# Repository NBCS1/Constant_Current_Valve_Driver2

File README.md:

# Constant_Current_Valve_Driver
Harware and firmware associated with controlling 4 bistable valves from TTL pulse of various duration. The Pulse is coming from a Pressure controller and its software were only the duration can be set. Different durations trigger different combinations of valves in the context of a microfluidic system.
The valves are bistable and require a pulse of constant current to turn ON/OFF. 
The code can be modified to have any pulse duration and the hardware can be modified to also obtain stable current from 0 to 1.5A.
The stable current is based on a AL8860 ic.

Disclaimer: We will not be responsible in case any implementation of the content of this repository leads to damage in instruments or components.

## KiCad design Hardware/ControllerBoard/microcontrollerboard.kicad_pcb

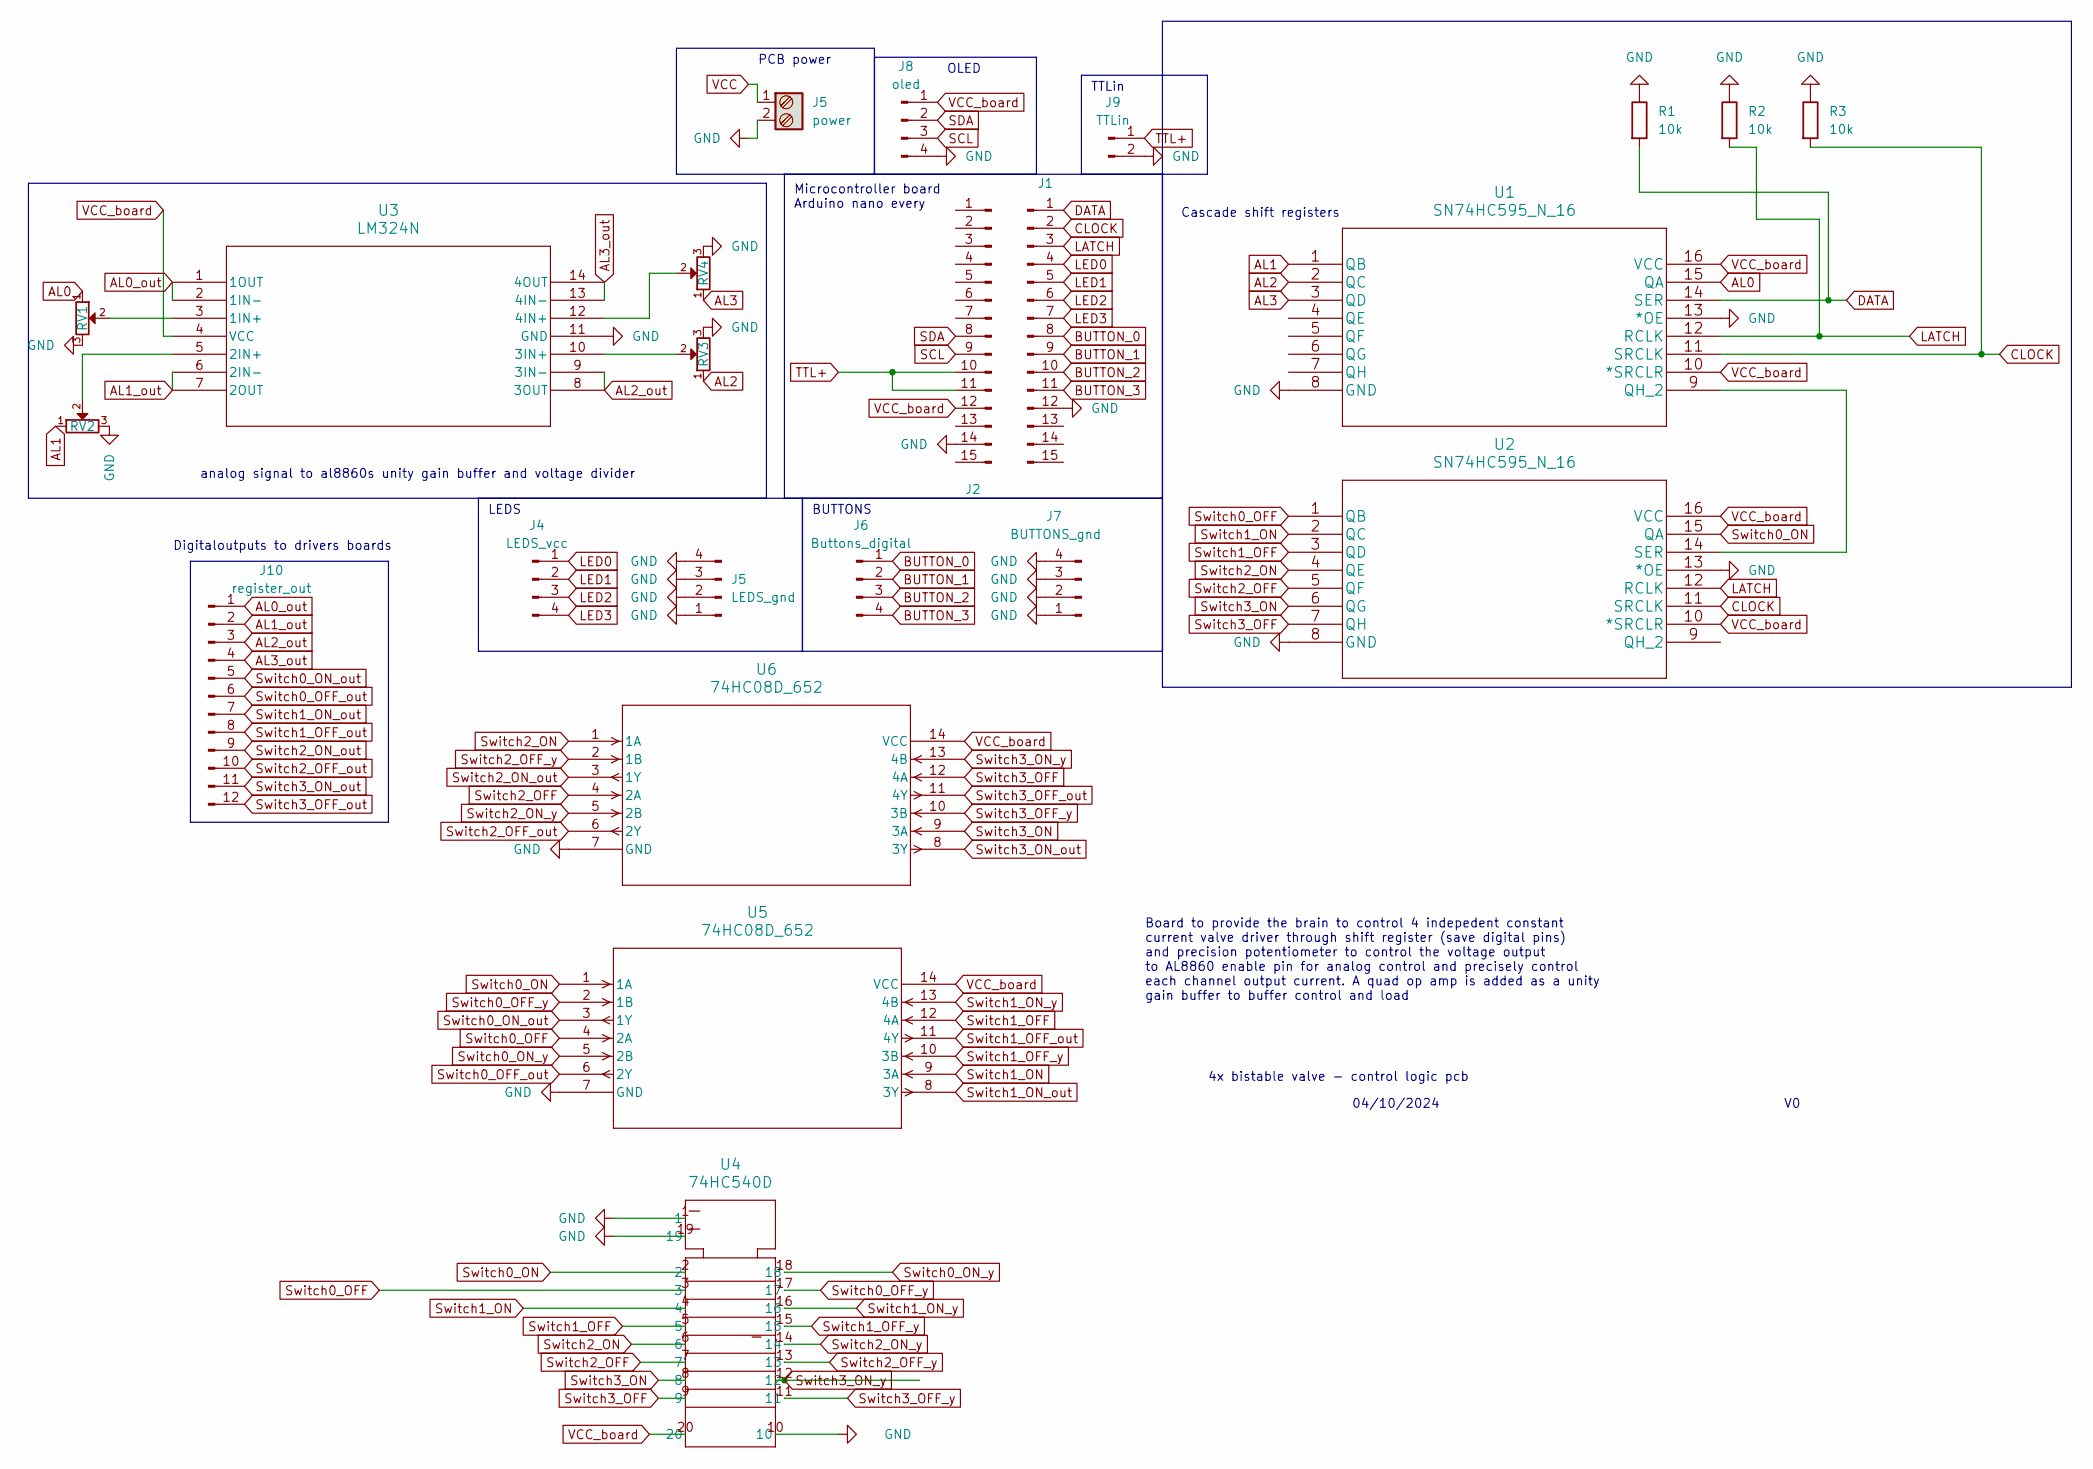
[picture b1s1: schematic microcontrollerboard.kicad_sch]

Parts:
J1, J2: Conn_01x15_Pin; PinHeader_1x15_P2.54mm_Vertical
J4: LEDS_vcc; PinSocket_1x04_P2.54mm_Vertical
J5: power; TerminalBlock_Phoenix_PT-1,5-2-5.0-H_1x02_P5.00mm_Horizontal
J6: Buttons_digital; PinSocket_1x04_P2.54mm_Vertical
J7: BUTTONS_gnd; PinSocket_1x04_P2.54mm_Vertical
J8: oled; PinSocket_1x04_P2.54mm_Vertical
J9: TTLin; PinSocket_1x02_P2.54mm_Vertical
J10: register_out; PinSocket_1x12_P2.54mm_Vertical
R1, R2, R3: 10k; R_1206_3216Metric_Pad1.30x1.75mm_HandSolder
RV1, RV2, RV3, RV4: potentiometer_3362P; Potentiometer_Vishay_T73XW_Horizontal
U1, U2: SN74HC595_N_16; D16-M
U3: LM324N; D14-M
U4: 74HC540D; SOIC20
U5, U6: 74HC08D_652; SOT108-1_NEX-M

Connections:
AL0: RV1.1, U1.15 (QA)
AL0_out: J10.1, U3.1 (1OUT), U3.2 (1IN-)
AL1: RV2.1, U1.1 (QB)
AL1_out: J10.2, U3.6 (2IN-), U3.7 (2OUT)
AL2: RV3.1, U1.2 (QC)
AL2_out: J10.3, U3.8 (3OUT), U3.9 (3IN-)
AL3: RV4.1, U1.3 (QD)
AL3_out: J10.4, U3.13 (4IN-), U3.14 (4OUT)
BUTTON_0: J1.8, J6.1
BUTTON_1: J1.9, J6.2
BUTTON_2: J1.10, J6.3
BUTTON_3: J1.11, J6.4
CLOCK: J1.2, R3.2, U1.11 (SRCLK), U2.11 (SRCLK)
DATA: J1.1, R1.2, U1.14 (SER)
LATCH: J1.3, R2.2, U1.12 (RCLK), U2.12 (RCLK)
LED0: J1.4, J4.1
LED1: J1.5, J4.2
LED2: J1.6, J4.3
LED3: J1.7, J4.4
unnamed: U1.9 (QH_2), U2.14 (SER)
unnamed: RV1.2, U3.3 (1IN+)
unnamed: RV2.2, U3.5 (2IN+)
unnamed: RV3.2, U3.10 (3IN+)
unnamed: RV4.2, U3.12 (4IN+)
SCL: J2.9, J8.3
SDA: J2.8, J8.2
Switch0_OFF: U2.1 (QB), U4.3, U5.4 (2A)
Switch0_OFF_out: J10.6, U5.6 (2Y)
Switch0_OFF_y: U4.17, U5.2 (1B)
Switch0_ON: U2.15 (QA), U4.2, U5.1 (1A)
Switch0_ON_out: J10.5, U5.3 (1Y)
Switch0_ON_y: U4.18, U5.5 (2B)
Switch1_OFF: U2.3 (QD), U4.5, U5.12 (4A)
Switch1_OFF_out: J10.8, U5.11 (4Y)
Switch1_OFF_y: U4.15, U5.10 (3B)
Switch1_ON: U2.2 (QC), U4.4, U5.9 (3A)
Switch1_ON_out: J10.7, U5.8 (3Y)
Switch1_ON_y: U4.16, U5.13 (4B)
Switch2_OFF: U2.5 (QF), U4.7, U6.4 (2A)
Switch2_OFF_out: J10.10, U6.6 (2Y)
Switch2_OFF_y: U4.13, U6.2 (1B)
Switch2_ON: U2.4 (QE), U4.6, U6.1 (1A)
Switch2_ON_out: J10.9, U6.3 (1Y)
Switch2_ON_y: U4.14, U6.5 (2B)
Switch3_OFF: U2.7 (QH), U4.9, U6.12 (4A)
Switch3_OFF_out: J10.12, U6.11 (4Y)
Switch3_OFF_y: U4.11, U6.10 (3B)
Switch3_ON: U2.6 (QG), U4.8, U6.9 (3A)
Switch3_ON_out: J10.11, U6.8 (3Y)
Switch3_ON_y: U4.12, U6.13 (4B)
TTL+: J2.10, J2.11, J9.1
VCC_board: J2.12, J8.1, U1.10 (*SRCLR), U1.16 (VCC), U2.10 (*SRCLR), U2.16 (VCC), U3.4 (VCC), U4.20, U5.14 (VCC), U6.14 (VCC)

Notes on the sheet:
Digitaloutputs to drivers boards
Cascade shift registers
04/10/2024
Board to provide the brain to control 4 indepedent constant current valve driver through shift register (save digital pins) and precision potentiometer to control the voltage output to AL8860 enable pin for analog control and precisely control each channel output current. A quad op amp is added as 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
PCB power
BUTTONS
OLED
Microcontroller board Arduino nano every
analog signal to al8860s unity gain buffer and voltage divider
LEDS
TTLin
4x bistable valve - control logic pcb

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
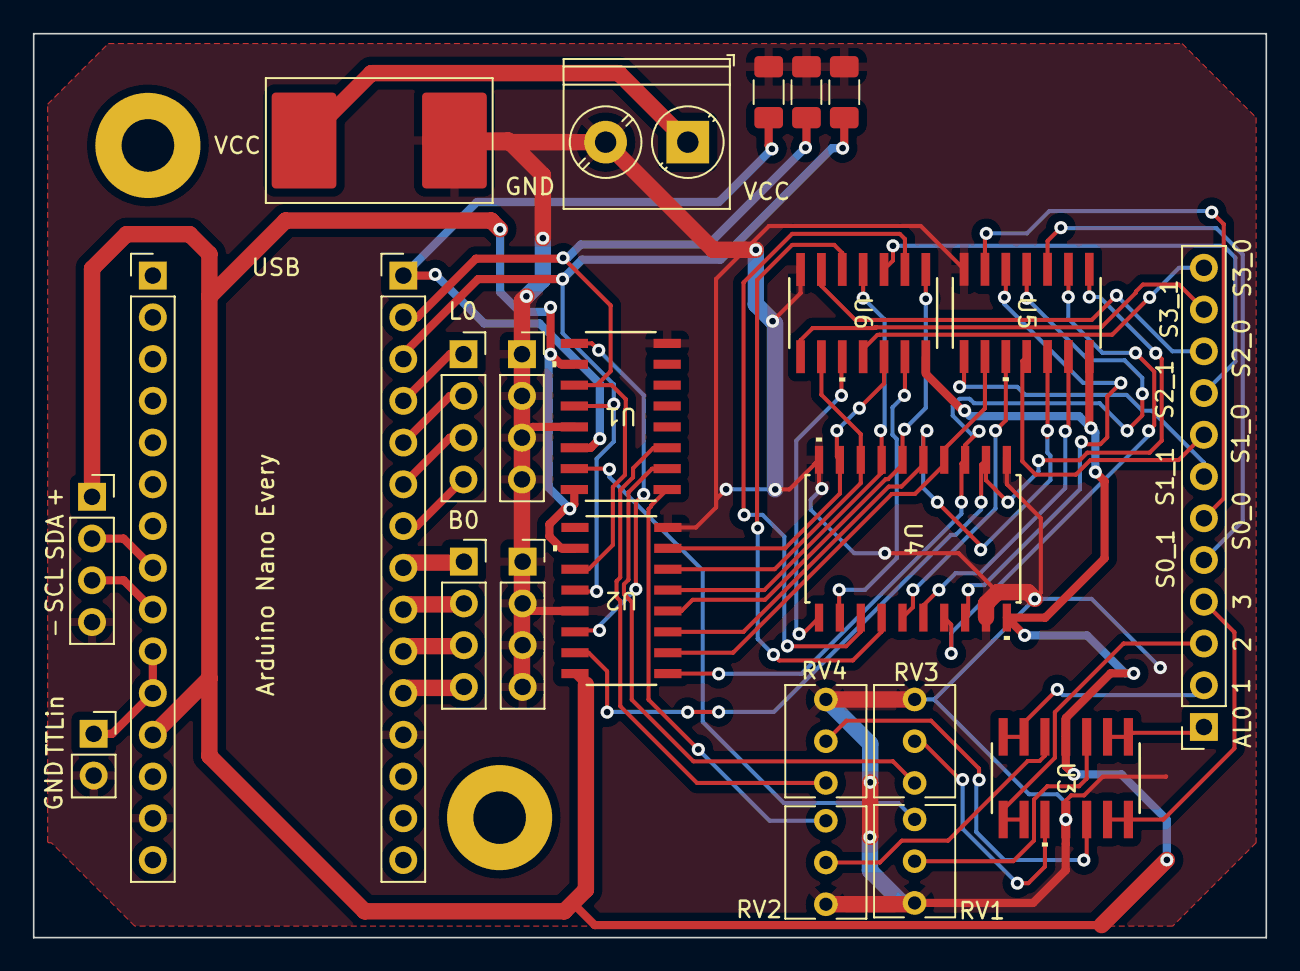
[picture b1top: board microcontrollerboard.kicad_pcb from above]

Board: 2 copper layers, 75.0 x 55.0 mm, 23 parts (0 on the bottom side), 53 nets.

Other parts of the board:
J3: power; TerminalBlock_Phoenix_PT-1,5-2-5.0-H_1x02_P5.00mm_Horizontal

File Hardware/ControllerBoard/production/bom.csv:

Designator;Footprint;Quantity;Value;LCSC Part #
J1, J2;PinHeader_1x15_P2.54mm_Vertical;2;Conn_01x15_Pin;
J10;PinSocket_1x12_P2.54mm_Vertical;1;register_out;
J3;TerminalBlock_Phoenix_PT-1,5-2-5.0-H_1x02_P5.00mm_Horizontal;1;power;
J4;PinSocket_1x04_P2.54mm_Vertical;1;LEDS_vcc;
J5;PinSocket_1x04_P2.54mm_Vertical;1;LEDS_gnd;
J6;PinSocket_1x04_P2.54mm_Vertical;1;Buttons_digital;
J7;PinSocket_1x04_P2.54mm_Vertical;1;BUTTONS_gnd;
J8;PinSocket_1x04_P2.54mm_Vertical;1;oled;
J9;PinSocket_1x02_P2.54mm_Vertical;1;TTLin;
R1, R2, R3;1206;3;10k;
RV1, RV2, RV3, RV4;Potentiometer_Vishay_T73XW_Horizontal;4;potentiometer_3362P;
U1, U2;D16-M;2;SN74HC595_N_16;
U3;D14-M;1;LM324N;
U4;SOIC20;1;74HC540D;
U5, U6;SOT108-1_NEX-M;2;74HC08D_652;

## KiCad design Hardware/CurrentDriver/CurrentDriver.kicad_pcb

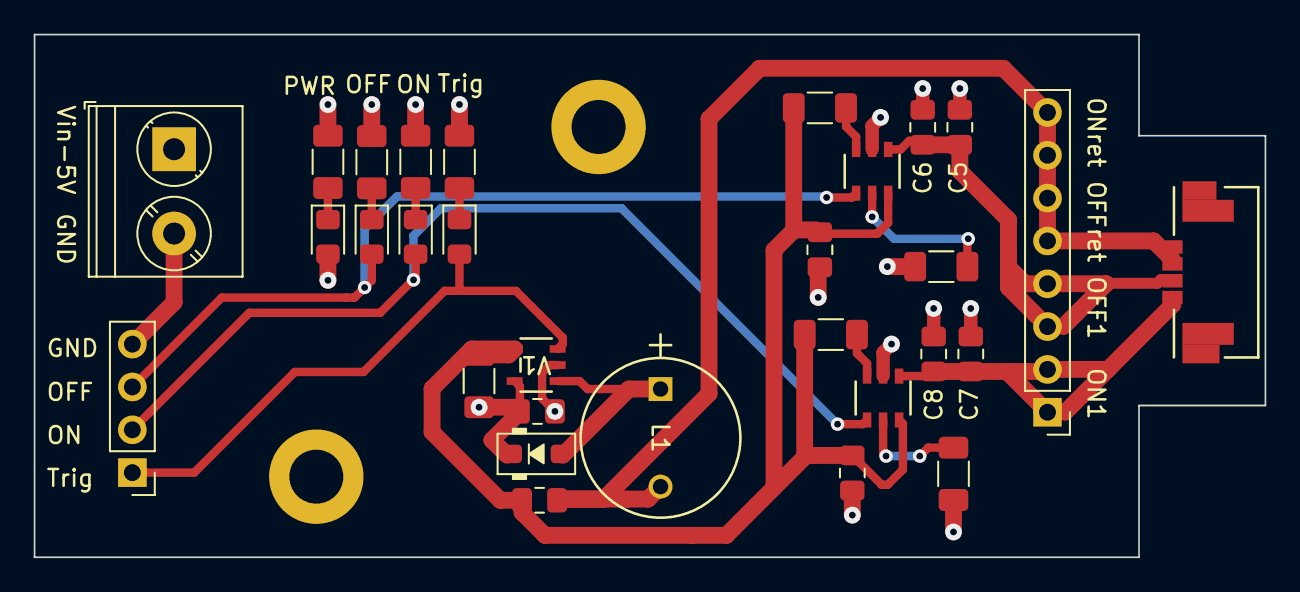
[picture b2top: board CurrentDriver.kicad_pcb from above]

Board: 4 copper layers, 73.0 x 31.0 mm, 30 parts (0 on the bottom side), 18 nets.

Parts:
C1, C2, C3, C4: C10µF_0805; C_0805_2012Metric_Pad1.18x1.45mm_HandSolder
C5, C7: C0.100µF_0805; C_0805_2012Metric_Pad1.18x1.45mm_HandSolder
C6, C8: C0.0.1µF_0805; C_0805_2012Metric_Pad1.18x1.45mm_HandSolder
D1: SS24FL; D_SOD-123F
D2, D4, D6, D7: LG R971-KN1; LED_0805_2012Metric_Pad1.15x1.40mm_HandSolder
J1: Conn_01x04; PinHeader_1x04_P2.54mm_Vertical
J3: power; TerminalBlock_Phoenix_PT-1,5-2-5.0-H_1x02_P5.00mm_Horizontal
J4: 527460871; CON_527460871_MOL
J10: Conn_01x08; PinHeader_1x08_P2.54mm_Vertical
L1: RLB0914-37µH; IND_BOURNS_RLB0914
R1: R125m_1206; R_1206_3216Metric_Pad1.30x1.75mm_HandSolder
R2, R3: 7kohms; R_1206_3216Metric_Pad1.30x1.75mm_HandSolder
R4, R5: 10kohms; R_1206_3216Metric_Pad1.30x1.75mm_HandSolder
R6, R8, R10, R11: 150ohms; R_1206_3216Metric_Pad1.30x1.75mm_HandSolder
U1, U2: AP22615AWU-7; TSOT26-P7_DIO
V1: AL8860WT; TSOT25_WT_DIO

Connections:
AP_+_1: C1.2, C3.2, C4.2, R1.1, R4.2, R5.2, U1.6 (in), U2.6 (in), V1.4 (SET)
AP_-_1: C1.1, J4.5, J4.6, J4.7, J4.8, J10.5, J10.6, J10.7, J10.8, L1.2
GND: C2.2, C3.1, C4.1, C5.1, C6.1, C7.1, C8.1, J1.4, J3.2, R2.2, R3.2, R6.2, R8.2, R10.2, R11.2, U1.2 (gnd), U2.2 (gnd), V1.2 (GND)
unnamed: D1.2 (A), L1.1, V1.1 (SW)
unnamed: D2.1 (K), R6.1
unnamed: D4.1 (K), R8.1
unnamed: D6.1 (K), R10.1
unnamed: D7.1 (K), R11.1
unnamed: R5.1, U1.3 (flg)
unnamed: R2.1, U1.5 (iset)
unnamed: R4.1, U2.3 (flg)
unnamed: R3.1, U2.5 (iset)
VCC: C2.1, D1.1 (K), D4.2 (A), J3.1, R1.2, V1.5 (VIN)
VtrigAL_1: D2.2 (A), J1.1, V1.3 (CTRL)
VtrigOFF_1: D7.2 (A), J1.3, U2.4 (en)
VtrigON_1: D6.2 (A), J1.2, U1.4 (en)
load_off_1: C5.2, C6.2, J4.3, J4.4, J10.3, J10.4, U2.1 (out)
load_on_1: C7.2, C8.2, J4.1, J4.2, J10.1, J10.2, U1.1 (out)

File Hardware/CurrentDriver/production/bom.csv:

Designator,Footprint,Quantity,Value,LCSC Part #
"C1, C2, C3, C4",0805,4,C10µF_0805,
"C5, C7",0805,2,C0.100µF_0805,
"C6, C8",0805,2,C0.0.1µF_0805,
D1,D_SOD-123F,1,SS24FL,
"D2, D4, D6, D7",0805,4,"
LG R971-KN1",
J1,PinHeader_1x04_P2.54mm_Vertical,1,Conn_01x04,
J10,PinHeader_1x08_P2.54mm_Vertical,1,Conn_01x08,
J3,"TerminalBlock_Phoenix_PT-1,5-2-5.0-H_1x02_P5.00mm_Horizontal",1,power,
J4,CON_527460871_MOL,1,527460871,
L1,IND_BOURNS_RLB0914,1,RLB0914-37µH,
R1,1206,1,R125m_1206,
"R10, R11, R6, R8",1206,4,150ohms,
"R2, R3",1206,2,7kohms,
"R4, R5",1206,2,10kohms,
"U1, U2",TSOT26-P7_DIO,2,AP22615AWU-7,
V1,TSOT25_WT_DIO,1,AL8860WT,

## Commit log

2025-01-01 Commit1
